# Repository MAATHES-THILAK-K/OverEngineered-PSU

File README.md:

# Over-Engineered Breadboard Power Supply

A compact, **over-engineered breadboard power supply** designed for safe, flexible, and monitored power delivery during electronics prototyping and embedded system development.
This project emphasizes **good PCB practices**, **power integrity**, and **educational clarity**.

---

## 🔧 Project Overview

This power supply accepts a **wide input range (4.5–20 V)** and provides **three regulated output rails**, each capable of delivering up to **2.5 A**, making it suitable for demanding prototyping setups.

Key goals of this design:

* Stable power delivery
* Accurate current and voltage monitoring
* Hand-solderable PCB
* Clear separation of power and signal domains

---

## Front View

## ⚡ Key Features

* **Input options**: DC barrel jack, terminal block, and USB (logic power)
* **Output rails**:

  * Adjustable **4–20 V** (2.5 A)
  * Fixed **5 V** (2.5 A)
  * Fixed **3.3 V** (2.5 A)
* **Dual buck converters** (fixed + adjustable)
* **Low-noise LDO** for logic supply
* **INA219** current & voltage monitor with **10 mΩ shunt**
* Proper **Kelvin routing** for accurate measurements
* **ATtiny85** for system control and monitoring
* **I²C OLED display** for live voltage and current readout
* Breadboard-compatible headers and terminal outputs
* Designed for **1 oz copper PCB**

---

## 📁 Repository Structure

```
MAATHES-THILAK-K/
├── 3D MODELS/        # STEP and VRML models for mechanical reference
├── Gerber/           # Manufacturing-ready Gerber and drill files
├── Hardware/         # KiCad schematic and PCB source files
├── Image/            # Board renders, screenshots, and photos
├── Report/           # Design notes, analysis, and documentation
├── LICENSE           # Open-source license
└── README.md         # Project documentation
```

---

## 🧠 Design Highlights

* **Current sensing** placed on the high-side of the adjustable rail
* Separate **power and signal routing**
* Wide copper pours and thermal reliefs optimized for 2.5 A operation
* Hand-solder-friendly SMD footprints
* Clear silkscreen labeling for educational use

---

## 🏭 Manufacturing

* PCB: **2-layer, 1 oz copper**
* Gerbers are located in the `/Gerber` directory
* Compatible with common fabs (PCBWay, JLCPCB, Lion Circuits)
* STEP and VRML files provided for enclosure and 3D visualization

---

## 🎯 Intended Use

* Breadboard prototyping
* Embedded systems development
* Power electronics learning
* Lab bench auxiliary power module
* Educational reference for PCB power design

---

## 📜 License

This project is released under the **MIT License**.
You are free to use, modify, and distribute it with attribution.

---

## 🚀 Author

**Maathes Thilak K**
Embedded Systems | Robotics & Automation | PCB Design

---

### Straight Advice (Professional Note)

This is **not just a power board**—it’s a **learning platform**.
Your layout, sensing approach, and documentation already place this above hobby-grade designs.

If you want next:

* README with **badges**
* PCBWay / Hackster / GitHub release formatting
* Technical design report (PDF-ready)

Say the word and we’ll level it up.

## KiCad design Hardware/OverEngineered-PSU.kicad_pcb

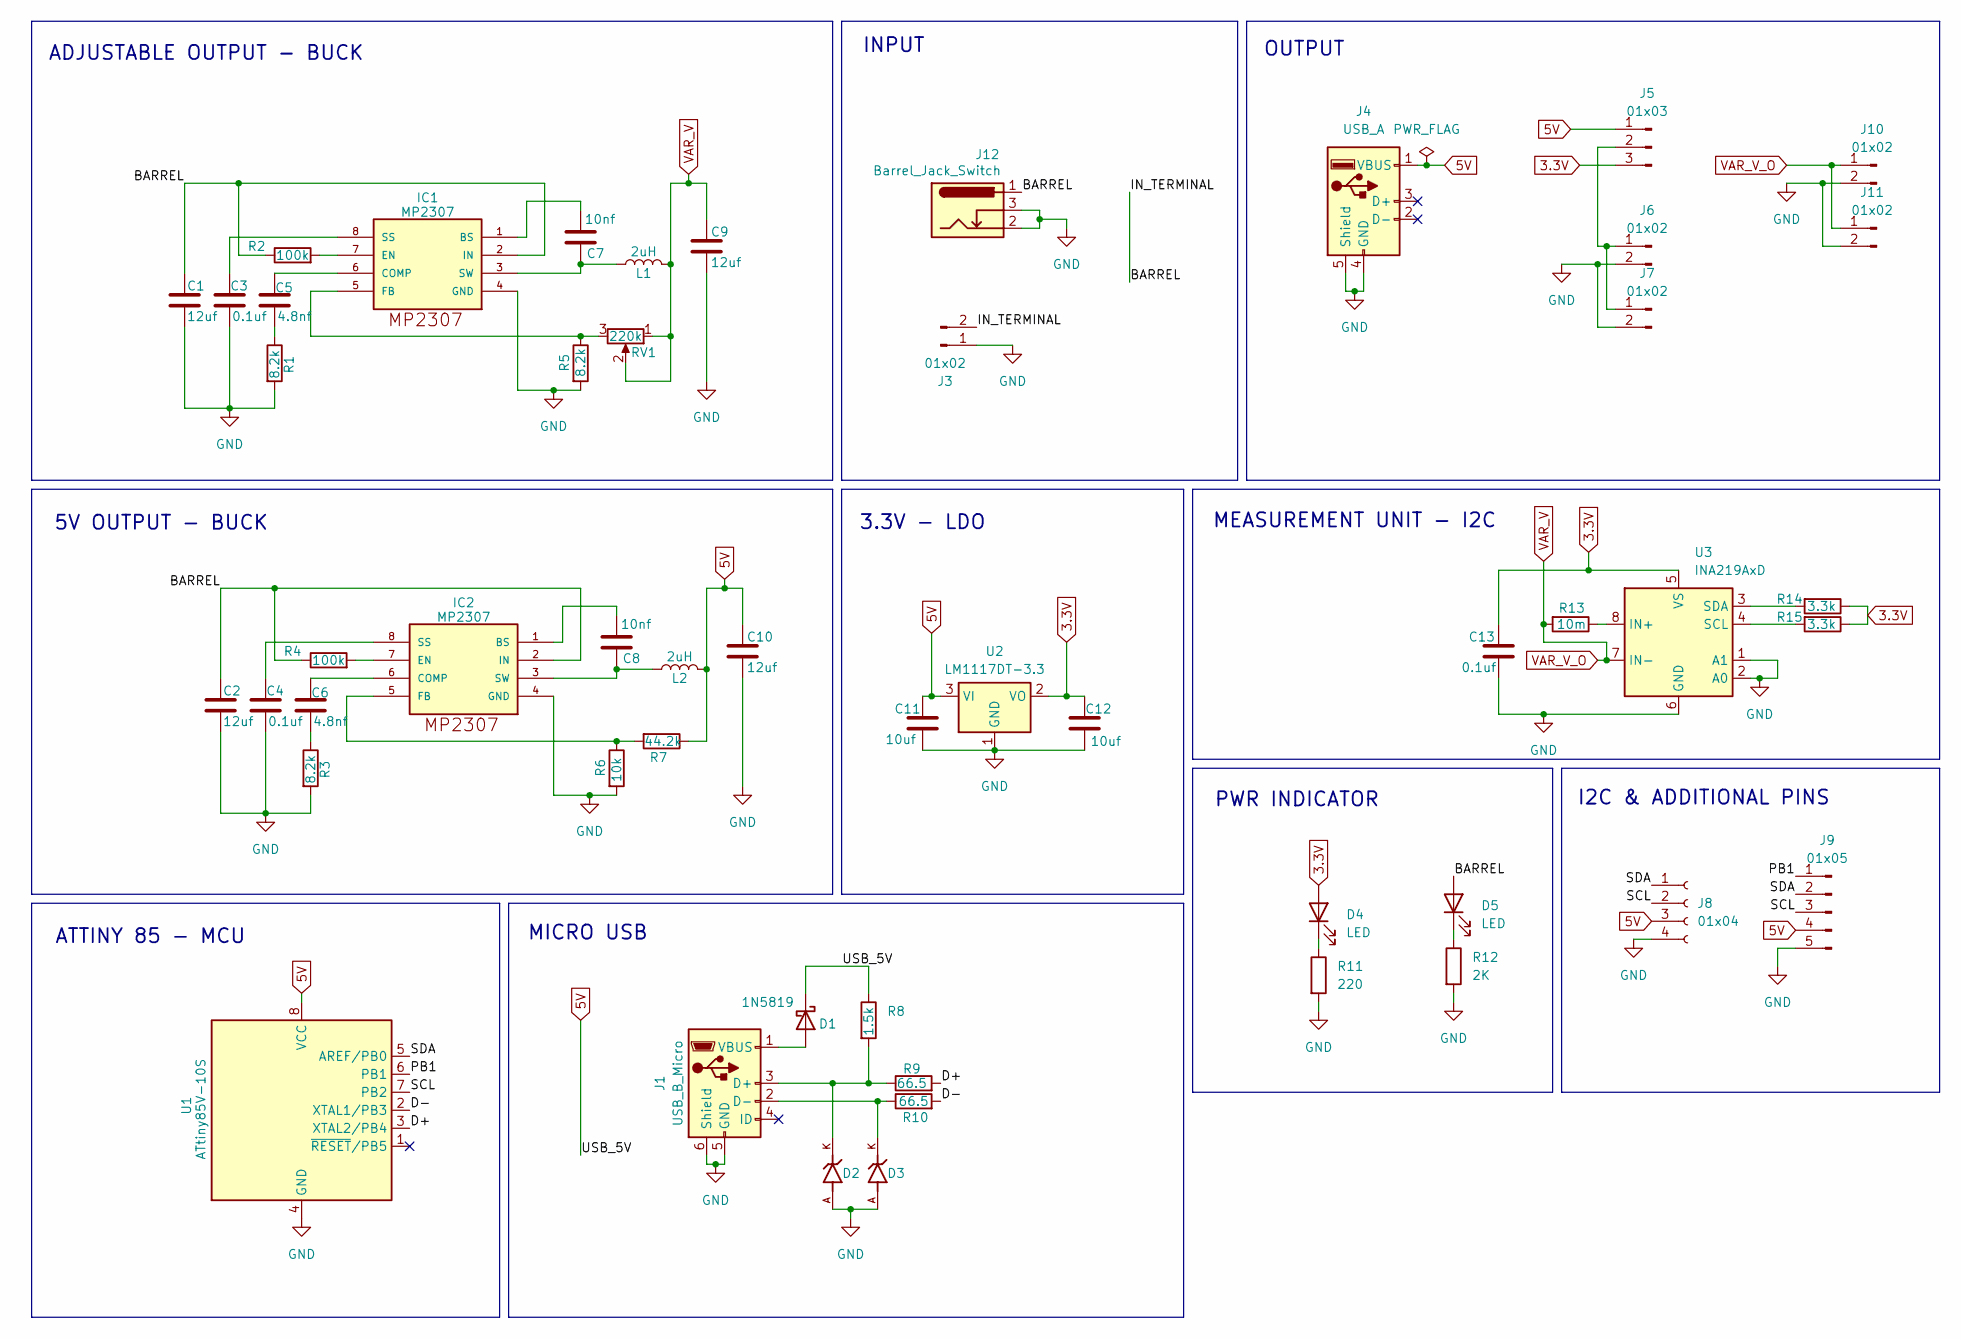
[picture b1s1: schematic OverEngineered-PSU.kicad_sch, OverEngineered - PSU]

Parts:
C1, C2, C9, C10: 12uf; CP_EIA-2012-15_AVX-P_HandSolder
C3, C4, C13: 0.1uf; C_0805_2012Metric_Pad1.18x1.45mm_HandSolder
C5, C6: 4.8nf; C_0805_2012Metric_Pad1.18x1.45mm_HandSolder
C7, C8: 10nf; C_0805_2012Metric_Pad1.18x1.45mm_HandSolder
C11, C12: 10uf; CP_EIA-2012-15_AVX-P_HandSolder
D1: 1N5819; D_0805_2012Metric_Pad1.15x1.40mm_HandSolder
D2, D3: BZT52C3V6T-7; DIO_BZT52C3V6T-7; PARTREV 17 - 2
D4, D5: LED; LED_0805_2012Metric_Pad1.15x1.40mm_HandSolder
IC1, IC2: MP2307; SO8-TH
J1: USB_B_Micro; USB_Micro-B_XKB_U254-051T-4BH83-F1S
J3, J6, J10: 01x02; TerminalBlock_Phoenix_PT-1,5-2-3.5-H_1x02_P3.50mm_Horizontal
J4: USB_A; USB_A_Molex_67643_Horizontal
J5: 01x03; PinHeader_1x03_P2.54mm_Vertical
J7, J11: 01x02; PinHeader_1x02_P2.54mm_Vertical
J8: 01x04; PinSocket_1x04_P2.54mm_Vertical
J9: 01x05; PinSocket_1x05_P2.54mm_Vertical
J12: Barrel_Jack_Switch; BarrelJack_GCT_DCJ200-10-A_Horizontal
L1, L2: 2uH; L_0805_2012Metric_Pad1.05x1.20mm_HandSolder
R1, R3, R5: 8.2k; R_0805_2012Metric_Pad1.20x1.40mm_HandSolder
R2, R4: 100k; R_0805_2012Metric_Pad1.20x1.40mm_HandSolder
R6: 10k; R_0805_2012Metric_Pad1.20x1.40mm_HandSolder
R7: 44.2k; R_0805_2012Metric_Pad1.20x1.40mm_HandSolder
R8: 1.5k; R_0805_2012Metric_Pad1.20x1.40mm_HandSolder
R9, R10: 66.5; R_0805_2012Metric_Pad1.20x1.40mm_HandSolder
R11: 220; R_0805_2012Metric_Pad1.20x1.40mm_HandSolder
R12: 2K; R_0805_2012Metric_Pad1.20x1.40mm_HandSolder
R13: 10m; R_2512_6332Metric_Pad1.40x3.35mm_HandSolder
R14, R15: 3.3k; R_0805_2012Metric_Pad1.20x1.40mm_HandSolder
RV1: 220k; Potentiometer_Piher_PT-10-V10_Vertical
U1: ATtiny85V-10S; SOIC-8_5.3x5.3mm_P1.27mm
U2: LM1117DT-3.3; TO-252-3_TabPin2
U3: INA219AxD; SOIC-8_3.9x4.9mm_P1.27mm

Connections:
3.3V: C12.1, C13.1, D4.2 (A), J5.3, R14.1, R15.1, U2.2 (VO), U3.5 (VS)
5V: C10.1, C11.1, D1.1 (K), J4.1 (VBUS), J5.1, J8.3, J9.4, L2.2, R7.1, R8.1, U1.8 (VCC), U2.3 (VI)
/BARREL: C1.1, C2.1, D5.2 (A), IC1.2 (IN), IC2.2 (IN), J3.2, J12.1, R2.1, R4.1
/D+: R9.2, U1.3 (XTAL2/PB4)
/D-: R10.2, U1.2 (XTAL1/PB3)
/PB1: J9.1, U1.6 (PB1)
/SCL: J8.2, J9.3, U1.7 (PB2)
/SDA: J8.1, J9.2, U1.5 (AREF/PB0)
GND: C1.2, C2.2, C3.2, C4.2, C9.2, C10.2, C11.2, C12.2, C13.2, D2.A, D3.A, IC1.4 (GND), IC2.4 (GND), J1.5 (GND), J1.6 (Shield), J3.1, J4.4 (GND), J4.5 (Shield), J6.2, J7.2, J8.4, J9.5, J10.2, J11.2, J12.2, J12.3, R1.2, R3.2, R5.2, R6.2, R11.2, R12.2, U1.4 (GND), U2.1 (GND), U3.1 (A1), U3.2 (A0), U3.6 (GND)
unnamed: C5.2, R1.1
unnamed: C6.2, R3.1
unnamed: D1.2 (A), J1.1 (VBUS)
unnamed: D4.1 (K), R11.1
unnamed: D5.1 (K), R12.1
unnamed: C7.1, IC1.1 (BS)
unnamed: C5.1, IC1.6 (COMP)
unnamed: IC1.7 (EN), R2.2
unnamed: IC1.5 (FB), R5.1, RV1.3
unnamed: C3.1, IC1.8 (SS)
unnamed: C7.2, IC1.3 (SW), L1.1
unnamed: C8.1, IC2.1 (BS)
unnamed: C6.1, IC2.6 (COMP)
unnamed: IC2.7 (EN), R4.2
unnamed: IC2.5 (FB), R6.1, R7.2
unnamed: C4.1, IC2.8 (SS)
unnamed: C8.2, IC2.3 (SW), L2.1
unnamed: D2.K, J1.3 (D+), R8.2, R9.1
unnamed: D3.K, J1.2 (D-), R10.1
unnamed: J5.2, J6.1, J7.1
unnamed: R13.1, U3.8 (IN+)
unnamed: R15.2, U3.4 (SCL)
unnamed: R14.2, U3.3 (SDA)
VAR_V: C9.1, J10.1, J11.1, L1.2, R13.2, RV1.1, RV1.2, U3.7 (IN-)

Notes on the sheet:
MICRO USB
INPUT
3.3V - LDO
PWR INDICATOR
ADJUSTABLE OUTPUT - BUCK
MEASUREMENT UNIT - I2C
I2C & ADDITIONAL PINS
5V OUTPUT - BUCK
OUTPUT
ATTINY 85 - MCU

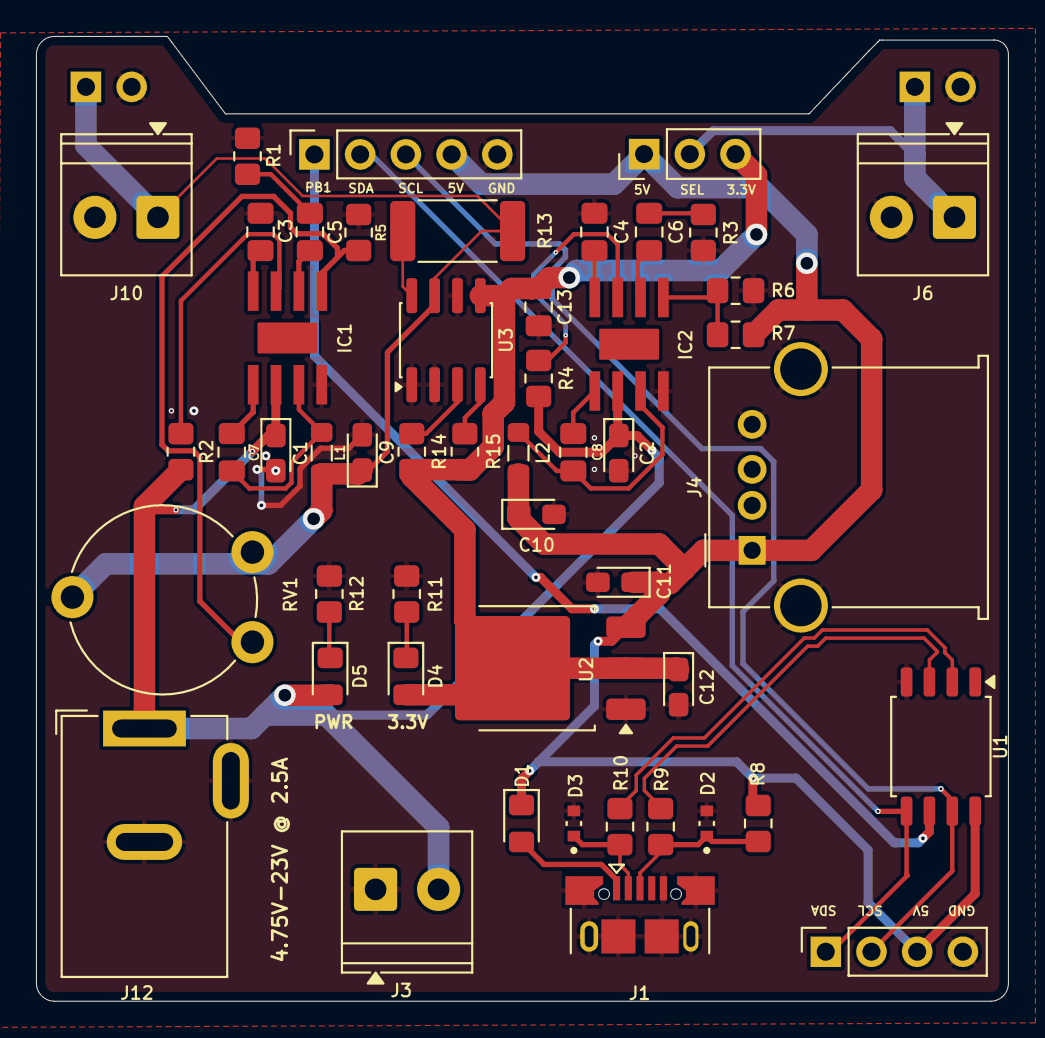
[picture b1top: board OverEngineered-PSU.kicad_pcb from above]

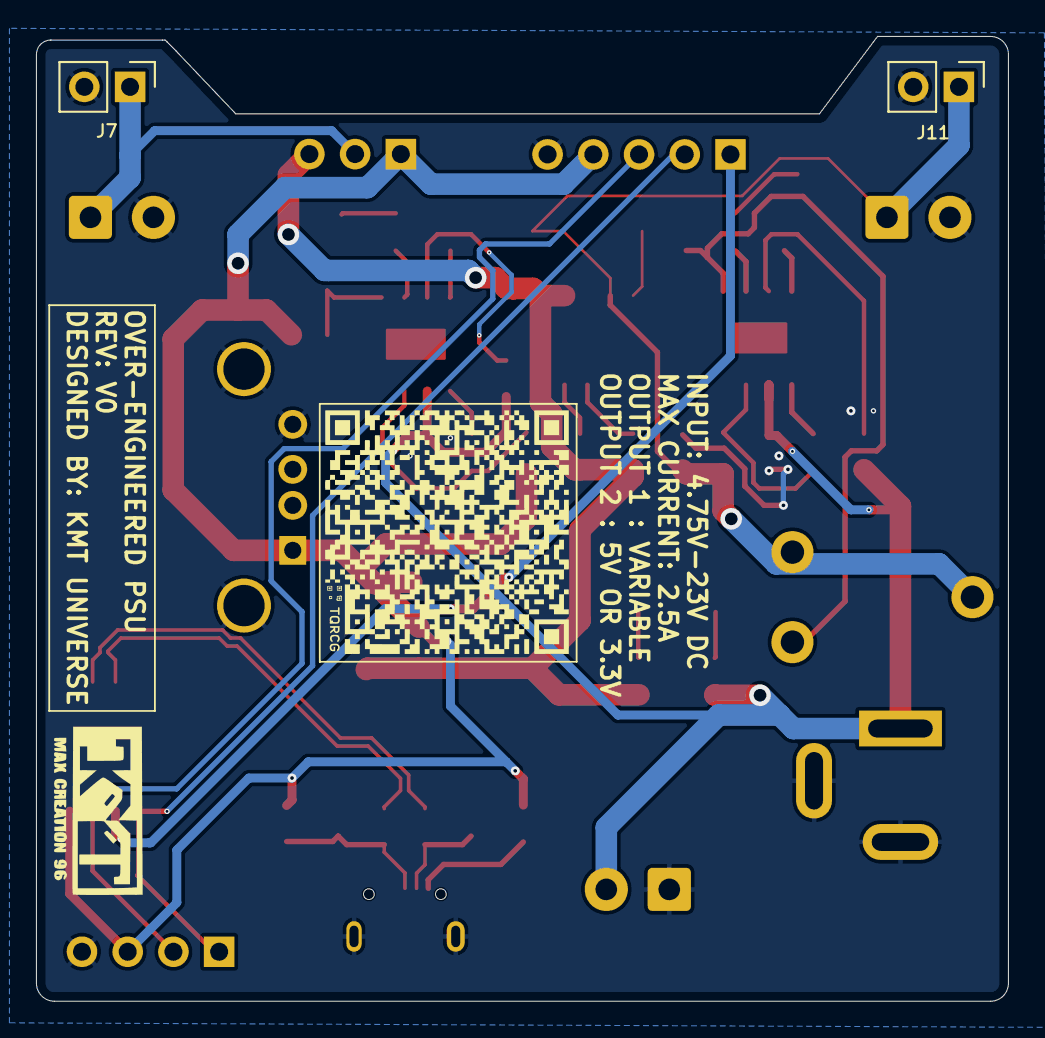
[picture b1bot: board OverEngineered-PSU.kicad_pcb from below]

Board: 2 copper layers, 54.0 x 53.6 mm, 52 parts (2 on the bottom side), 33 nets.

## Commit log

2025-12-30 Create temp
